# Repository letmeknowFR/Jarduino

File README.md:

<a href="#link"> _English version below_ :us: :arrow_down: </a>

> <p align="justify">Le Jarduino est un kit DIY permettant de créer un système de culture hydroponique et automatisé pour toutes sortes de plantes. Il permet de découvrir les concepts de l'agriculture hors-sol mais également de s'initier à l'électronique, la programmation, et l'impression 3D. Ce mini jardin est à faire soi-même. Modulable, personnalisable et évolutif selon vos envies, le Jarduino est Open Source : nous fournissons à tous les fichiers nécessaires pour réaliser les pieds, les panneaux latéraux et même la carte électronique. Il est donc très simple de s'approprier le projet afin de l'améliorer ou de le personnaliser.</p>

### Bill Of Materials :bookmark_tabs:
***
| Quantité |            Composant            |
|:--------:|:-------------------------------:|
|     1    | Carte électronique              |
|     1    | LCD 2 lignes 16 caractères I2C  |
|     1    | Jeu d'embases                   |
|     1    | Pompe USB                       |
|     1    | Lampe USB                       |
|     1    | Panier - Impression 3D          |
|     1    | Pied principal - Impression 3D  |
|     1    | Panneau supérieur               |
|     1    | Récipient                       |
|     1    | Durite                          |
|     1    | Alimentation                    |
|     3    | Pied angle - Impression 3D      |
|     4    | Panneaux latéraux               |

### Programmation :computer:
***
Tout d'abord placez la pile bouton (CR1220) dans son emplacement si cela n'est pas déjà fait. Ensuite, connectez l'écran à la carte principale via son connecteur, puis fixez-le à l'aide de l'embase prévue à cet effet.

Après avoir installé l'IDE Arduino, grâce au dossier fourni [software](/Software) ou directement sur le [site officiel](https://www.arduino.cc/en/Main/Software), installez les librairies qui se trouvent dans le dossier [librairies](/Software/Librairies) nécessaires à la compilation du programme principal "Jarduino.ino". Pour cela décompressez le contenu de l'archive dans votre répertoire Arduino/libraries.

Double-cliquez sur le programme ["Jarduino.ino"](/Software/Jarduino/Jarduino.ino).

Branchez votre carte via le connecteur USB, choisissez la carte "Leonardo" dans outils/type de carte et téléversez le programme !

Vous disposez également d'un programme de test ["Jarduino_test.ino"](/Software/Jarduino_Test/Jarduino_Test.ino). Il vous permettra de savoir si tous les composants électroniques fonctionnent correctement.

Vous voilà fin prêt ! Passons à la mécanique.

### Montage :wrench:
***
<p align="justify">Vous trouverez dans votre package mécanique: 3 pieds, 1 pied pour y placer la carte électronique, 4 panneaux de plastiques pour les côtés, 1 panneau pour le dessus. Montez le tout, remplissez 1/4 du récipient d'eau, ajoutez-y la lampe, la pompe, branchez l'alimentation et vous êtes fin prêt à faire pousser vos plantes.</p>

Vous pouvez bien sûr imprimer vos propres pieds et paniers grâce au dossier ["3D"](/3D).

### De la patience maintenant, la plante pousse ! :seedling:
***
***
<p align="center">  :us: </p>

>  <p align="justify">Jarduino is a DIY kit allowing to create a hydroponic and automated cultivation system for all kinds of plants . It allows to discover off-ground agriculture concepts and learn about electronics, programming, and 3D printing. This mini garden is a do it yourself project. Modular, customizable and scalable as you want, Jarduino is Open Source: we provide all necessary files to realize the feet, the side panels and even the electronic card. It's very simple to assimilate the project in order to improve it or to personalize it.</p>

### Bill Of Materials :bookmark_tabs:
***

| Quantity |            Components           |
|:--------:|:-------------------------------:|
|     1    | Electronic card                 |
|     1    | 2 line 16 character I2C LCD     |
|     1    | Header                          |
|     1    | USB Pump                        |
|     1    | USB Lamp                        |
|     1    | Basket - 3D printed             |
|     1    | Main foot - 3D printed          |
|     1    | Up pannel                       |
|     1    | Container                       |
|     1    | Hose                            |
|     1    | Alimentation                    |
|     3    | Angle foot - 3D printed         |
|     4    | Side pannel                     |

### Programming :computer:
***
First, place the button cell (CR1220) in its position if not already done. Then, connect the screen with the electronic card thanks to the 4-pin connector and fix it with the given headers.

After you installed Arduino, thanks to given folder ["software"](/Software) or the [official website](https://www.arduino.cc/en/Main/Software), install the libraries placed in the ["libraries"](/Software/Librairies) folder that make "Jarduino.ino" program compiled. To do that, uncompress the archive content in your Arduino/libraries folder.

Double-click on the program ["Jarduino.ino"](/Software/Jarduino/Jarduino.ino).

Connect the electronic card with your computer thank to the USB connector, choose "Leonardo" in tools/board option and upload the program!

You have a test program ["Jarduino_test.ino"](/Software/Jarduino_Test/Jarduino_Test.ino). It'll allow you to know if everything is ok.

You're all right! Let's move to the mechanical assembly.

### Mechanical assembly :wrench:
***
<p align="justify">You'll find in mechanical package: 3 feet, 1 main foot for the electronic card, 4 side panels, 1 panel for the top. Assemble it, fill a quarter of container with water, add the lamp, pump, power up and you're good to go!</p>

You can print your own 3D parts thanks to the given folder ["3D"](/3D).

### Patience now, plant is growing ! :seedling:

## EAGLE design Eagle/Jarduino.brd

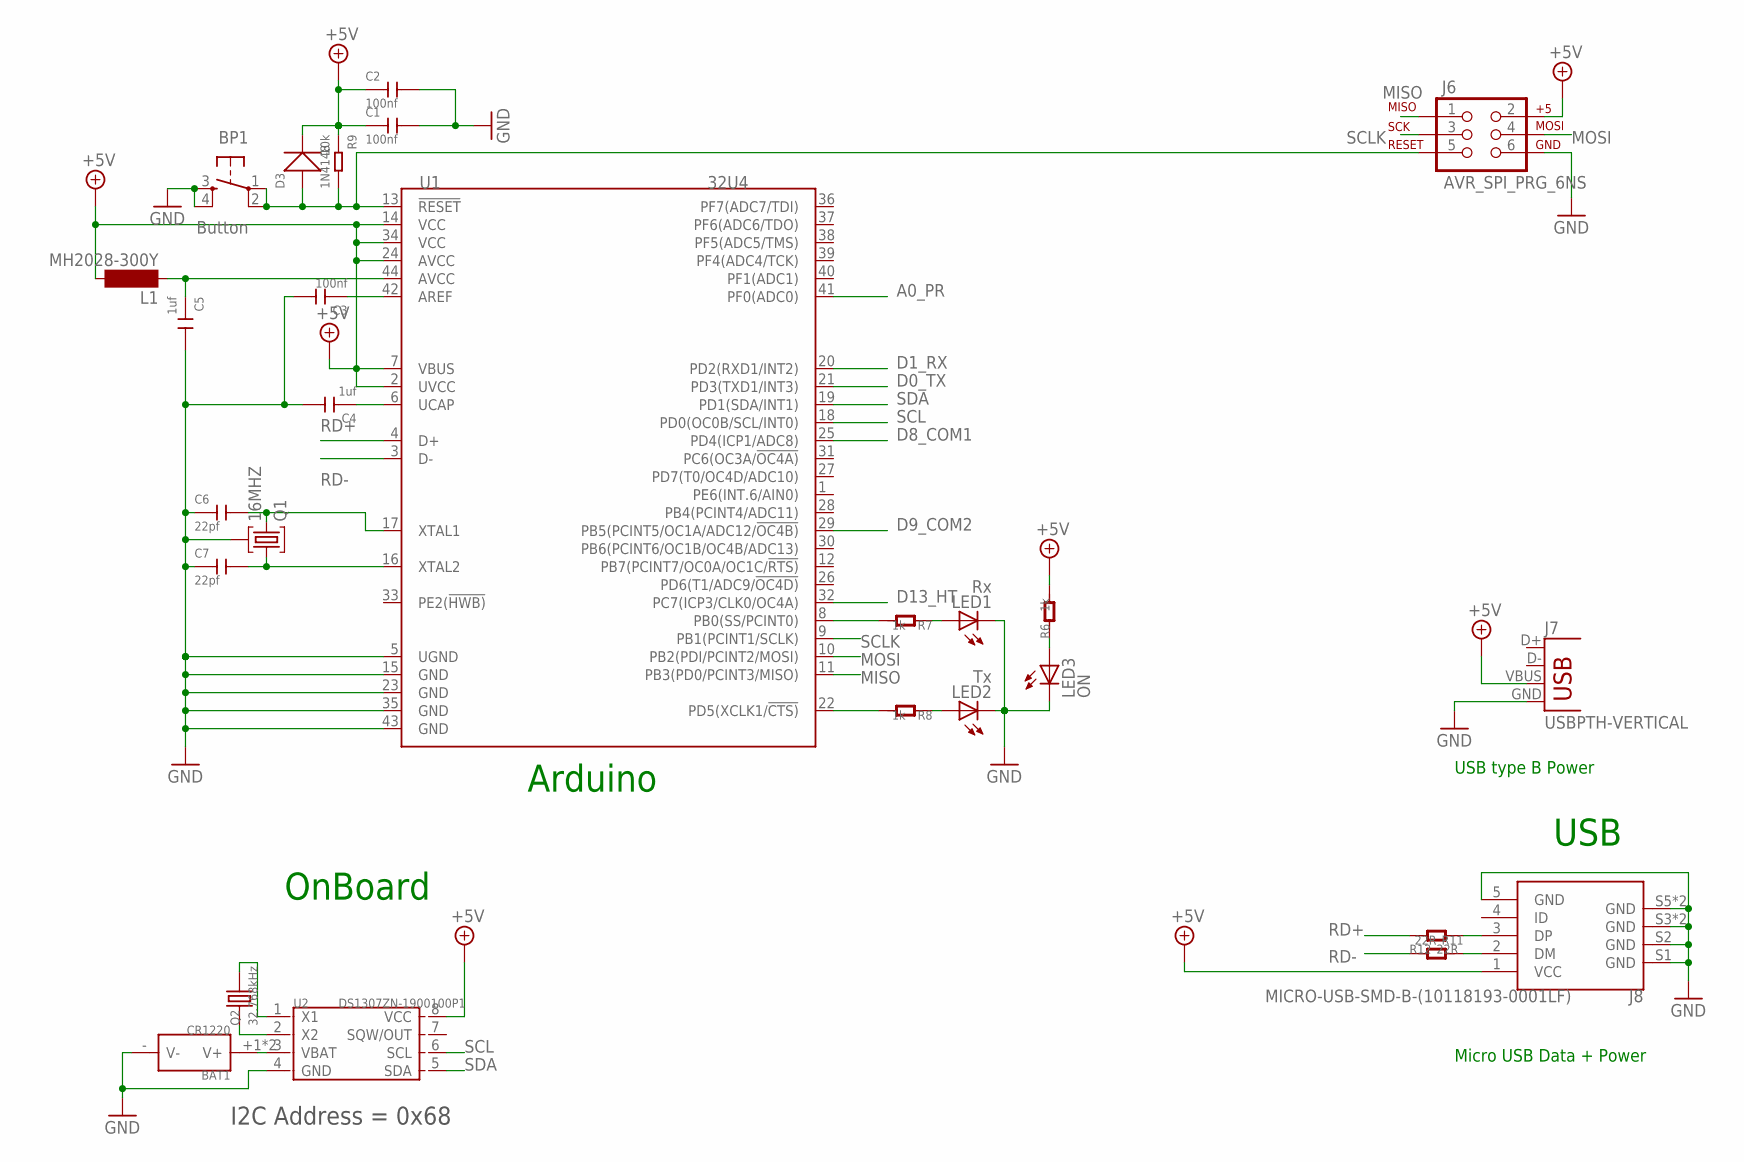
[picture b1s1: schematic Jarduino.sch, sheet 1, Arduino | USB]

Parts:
BAT1: CR1220; METAL-CR1220-D13.5XH5.0MM
BP1: Button; TACTILE-PTH
C1, C2, C3: 100nf; C0603
C4, C5: 1uf; C0603
C6, C7: 22pf; C0603
D3: 1N4148; LL-34
J6: AVR_SPI_PRG_6NS; 2X3-NS
J7: USBPTH-VERTICAL; USB-B-PTH-VERTICAL
J8: MICRO-USB-SMD-B-(10118193-0001LF); MICRO-USB5+6P-SMD-0.65-B
L1: MH2028-300Y; SM-1206
LED1: Rx; CHIP-LED0805
LED2: Tx; CHIP-LED0805
LED3: ON; CHIP-LED0805
Q1: 16MHZ; HC49U
Q2: 32.768kHz; 2P-L3.2XW1.5MM
R6, R7, R8: 1k; R0805
R9: 10k; R0805
R11, R12: 22R; R0805
U1: 32U4; TQFP44-0.8-9.6X9.6MM
U2: DS1307ZN-1900100P1; SOIC8

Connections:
+5V: C1.1, C2.1, D3.C (-), J6.2, J7.VBUS, J8.1 (VCC), L1.2, R6.2, R9.1, U1.2 (UVCC), U1.7 (VBUS), U1.14 (VCC), U1.24 (AVCC), U1.34 (VCC), U2.8 (VCC); also elsewhere on the board
A0_PR: U1.41 (PF0(ADC0)); also elsewhere on the board
D0_TX: U1.21 (PD3(TXD1/INT3)); also elsewhere on the board
D1_RX: U1.20 (PD2(RXD1/INT2)); also elsewhere on the board
D8_COM1: U1.25 (PD4(ICP1/ADC8)); also elsewhere on the board
D9_COM2: U1.29 (PB5(PCINT5/OC1A/ADC12/!OC4B)); also elsewhere on the board
D13_HT: U1.32 (PC7(ICP3/CLK0/OC4A)); also elsewhere on the board
GND: BAT1.- (V-), BP1.3, BP1.4, C1.2, C2.2, C3.2, C4.2, C5.2, C6.1, C7.1, J6.6, J7.GND, J8.5 (GND), J8.S1 (GND), J8.S2 (GND), J8.S3 (GND), J8.S4 (GND), J8.S5 (GND), J8.S6 (GND), LED1.C, LED2.C, LED3.C, Q1.2, U1.5 (UGND), U1.15 (GND), U1.23 (GND), U1.35 (GND), U1.43 (GND), U2.4 (GND); also elsewhere on the board
MISO: J6.1, U1.11 (PB3(PD0/PCINT3/MISO))
MOSI: J6.4, U1.10 (PB2(PDI/PCINT2/MOSI))
unnamed: LED3.A, R6.1
unnamed: R7.2, U1.8 (PB0(SS/PCINT0))
unnamed: J8.2 (DM), R12.2
unnamed: R8.2, U1.22 (PD5(XCLK1/!CTS))
unnamed: LED1.A, R7.1
unnamed: LED2.A, R8.1
unnamed: C6.2, Q1.3, U1.17 (XTAL1)
unnamed: C4.1, U1.6 (UCAP)
unnamed: C5.1, L1.1, U1.44 (AVCC)
unnamed: C3.1, U1.42 (AREF)
unnamed: C7.2, Q1.1, U1.16 (XTAL2)
unnamed: J8.3 (DP), R11.1
unnamed: Q2.2, U2.1 (X1)
unnamed: Q2.1, U2.2 (X2)
unnamed: BAT1.+1 (V+), BAT1.+2 (V+), U2.3 (VBAT)
RD+: R11.2, U1.4 (D+)
RD-: R12.1, U1.3 (D-)
RESET: BP1.1, BP1.2, D3.A (+), J6.5, R9.2, U1.13 (!RESET)
SCL: U1.18 (PD0(OC0B/SCL/INT0)), U2.6 (SCL); also elsewhere on the board
SCLK: J6.3, U1.9 (PB1(PCINT1/SCLK))
SDA: U1.19 (PD1(SDA/INT1)), U2.5 (SDA); also elsewhere on the board

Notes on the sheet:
Arduino
I2C Address = 0x68
OnBoard
USB
Micro USB Data + Power
USB type B Power

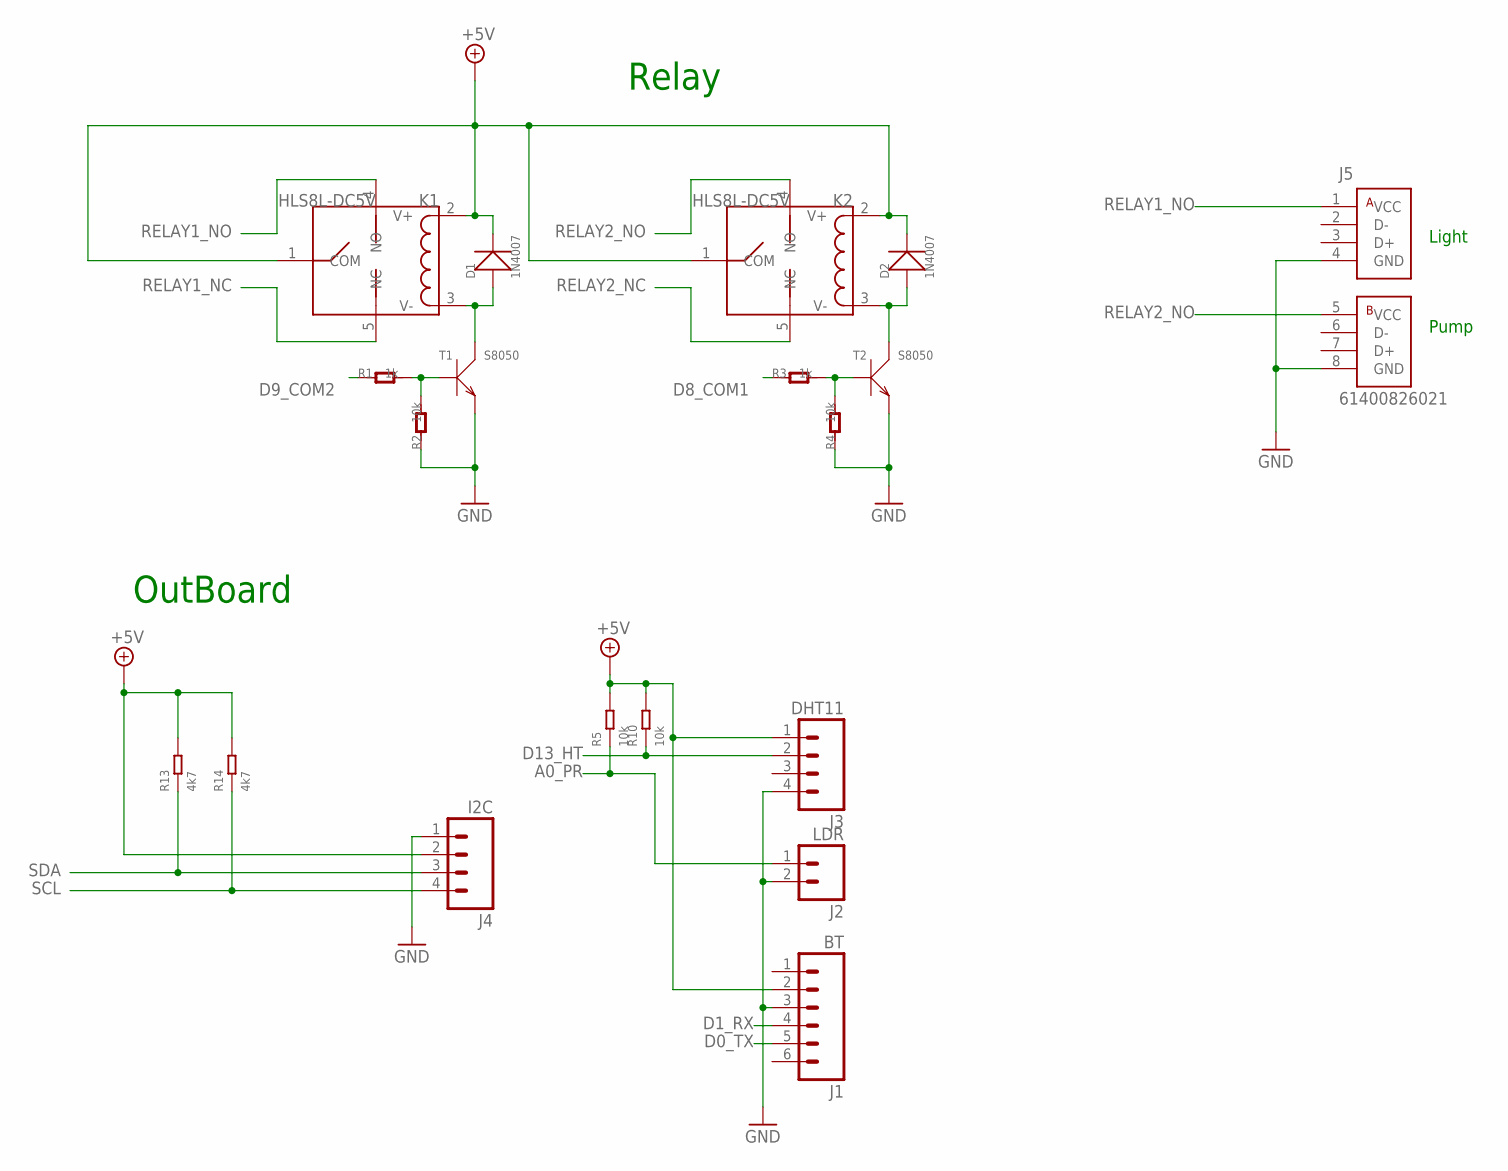
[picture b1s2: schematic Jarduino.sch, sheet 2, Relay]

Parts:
D1, D2: 1N4007; DO-214AC
J1: BT; MOLEX-1X6
J2: LDR; MOLEX-1X2
J3: DHT11; MOLEX-1X4
J4: I2C; MOLEX-1X4
J5: 61400826021
K1, K2: HLS8L-DC5V; 5P-L19.0XW15.0XH15.0MM
R1, R3: 1k; R0805
R2, R4, R5, R10: 10k; R0805
R13, R14: 4k7; R0805
T1, T2: S8050; SOT23

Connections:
+5V: D1.2 (-), D2.2 (-), J1.2, J3.1, J4.2, K1.1 (COM), K1.2 (V+), K2.1 (COM), K2.2 (V+), R5.2, R10.2, R13.2, R14.2; also elsewhere on the board
A0_PR: J2.1, R5.1; also elsewhere on the board
D0_TX: J1.5; also elsewhere on the board
D1_RX: J1.4; also elsewhere on the board
D8_COM1: R3.1; also elsewhere on the board
D9_COM2: R1.1; also elsewhere on the board
D13_HT: J3.2, R10.1; also elsewhere on the board
GND: J1.3, J2.2, J3.4, J4.1, J5.4 (GND), J5.8 (GND), R2.1, R4.1, T1.2 (E), T2.2 (E); also elsewhere on the board
unnamed: R3.2, R4.2, T2.1 (B)
unnamed: D2.1 (+), K2.3 (V-), T2.3 (C)
unnamed: R1.2, R2.2, T1.1 (B)
unnamed: D1.1 (+), K1.3 (V-), T1.3 (C)
RELAY1_NC: K1.5 (NC)
RELAY1_NO: J5.1 (VCC), K1.4 (NO)
RELAY2_NC: K2.5 (NC)
RELAY2_NO: J5.5 (VCC), K2.4 (NO)
SCL: J4.4, R14.1; also elsewhere on the board
SDA: J4.3, R13.1; also elsewhere on the board

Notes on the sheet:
Relay
OutBoard
Light
Pump

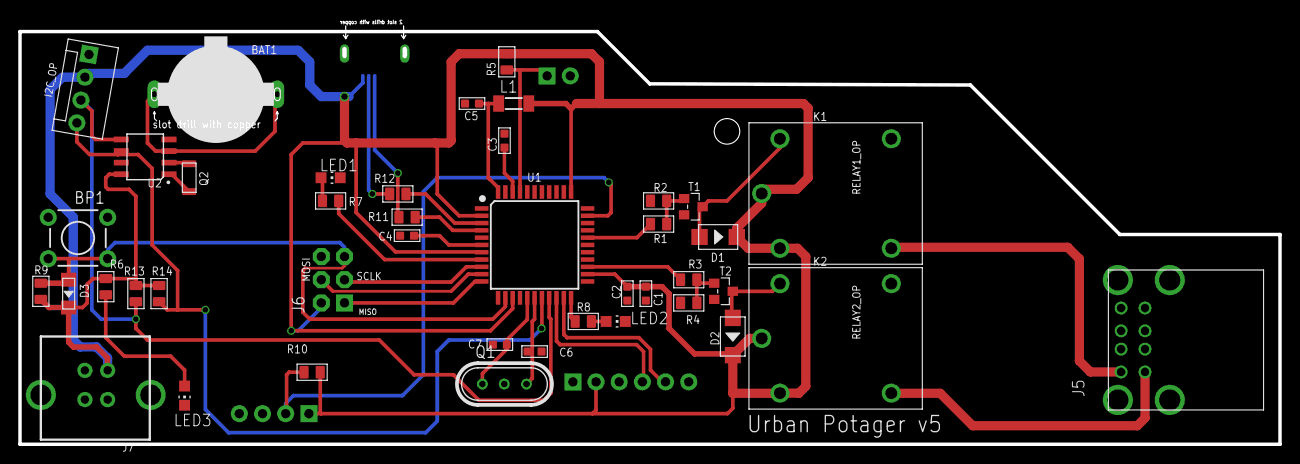
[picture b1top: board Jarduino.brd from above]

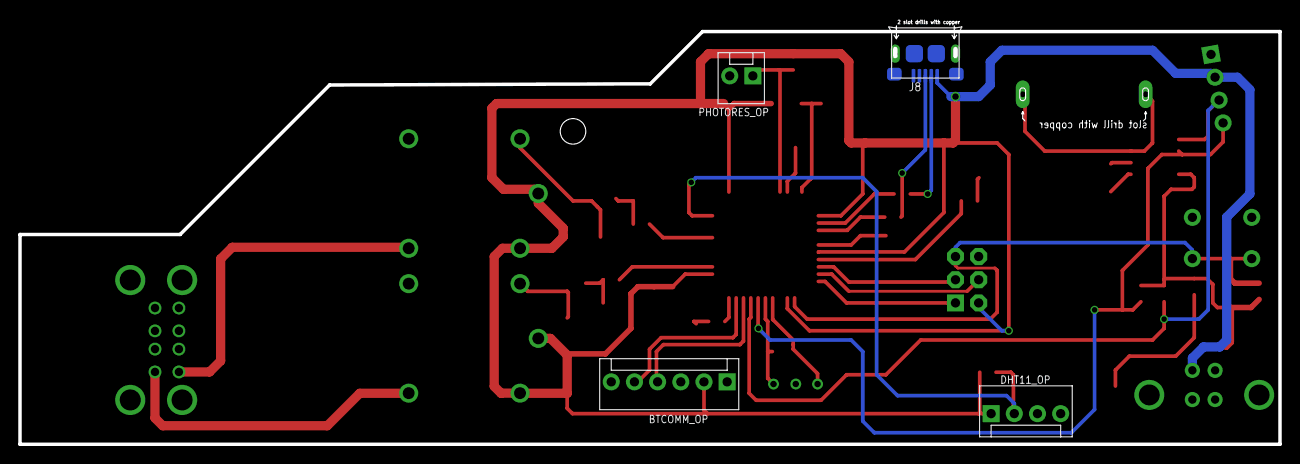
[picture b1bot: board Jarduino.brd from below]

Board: 2 copper layers, 137.9 x 46.4 mm, 46 parts (4 on the bottom side), 37 nets.

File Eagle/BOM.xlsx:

Name | Part | Value | Package | Description | Part NO. | Band
BAT1 | Battery holder | CR1220 | METAL-CR1220-D13.5XH5.0MM | Battery CR1220 holder
BP1 | Button | TAC_SWITCHPTH | TACTILE-PTH | Push button
C1, C2, C3 | Capacitor | 100nf 50V 10% | C0603 | Capacitor
C4, C5 | Capacitor | 100µf 50V 10% | C0603 | Capacitor
C6, C7 | Capacitor | 22pf 50V 10% | C0603 | Capacitor
D1, D2 | Diode | 1N4007 | DO-214AC | Diode
D3 | Diode | 1N4148 | LL-34 | Diode
J1 | Connector | M06POLAR | MOLEX-1X6 | Connector 6 points | Not implemented | Not implemented
J2 | Connector | M02POLAR | MOLEX-1X2 | Connector 2 points | Not implemented | Not implemented
J3, J4 | Connector | M04POLAR | MOLEX-1X4 | Connector 4 points | Not implemented | Not implemented
J5 | Connector | Double USB connector | 61400826021 | Double USB connector
J6 | Connector | AVR_SPI_PRG_6NS | 2X3-NS | Connector 2x3 points
J7 | Connector | USBPTH-VERTICAL | USB-B-PTH-VERTICAL | Connector USB type B vertical
J8 | Connector | MICRO-USB-SMD-B-(10118193-0001LF) | MICRO-USB5SMD-0.65-B Seee | Micro USB connector
K1, K2 | Relay | RELAY-HLS8L-DC5V-S-C-315030000 | 5P-L19.0XW15.0XH15.0MM | Relay 5V
L1 | Inductor | MH2028-300Y | SM-1206 | Inductor | Not implemented | Not implemented
LED1 | Rx | LEDCHIP-LED0805 | CHIP-LED0805 | led | Red LED | Generic
LED2 | Tx | LEDCHIP-LED0805 | CHIP-LED0805 | led | Red LED | Generic
LED3 | ON | LEDCHIP-LED0805 | CHIP-LED0805 | led | Green LED | Generic
Q1 | crystal | 16MHZ | HC49U | crystal
Q2 | crystal | 32.768kHz | 2P-L3.2XW1.5MM | crystal
R1, R3, R6, R7, R8 | Resistor | 1k | R0805 | Resistor | 1k | Generic
R2, R4, R5, R9, R10 | Resistor | 10k | R0805 | Resistor | 10k | Generic
R11, R12 | Resistor | 22R | R0805 | Resistor | 22R | Generic
R13, R14 | Resistor | 4k7 | R0805 | Resistor | 4k7 | Generic
T1, T2 | Transistor | S8050 | SOT23 | Transistor
U1 | Micro-controler | MCU-ATMEGA32U4(TQFP44)-AU | TQFP44-0.8-9.6X9.6MM | Micro-controler | ATMEGA32U4 | ATMEGA
U2 | RTC | DS1307ZN-1900100P1 | SOIC8 | RTC IC | DS1307ZN

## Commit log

2016-11-15 Add files
2017-10-18 Readme modif'
2017-12-03 Add Freecad files
    Freecad sources of the STL files
2018-02-28 Fixed a bug where the RTC would go back to the time/date of compilation after MCU reset. Ticket #310933
2018-05-29 Mise à jour des fichiers d'impressions
2018-08-01 adding small unit test of different components

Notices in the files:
parts and their libraries:
SparkFun-Connectors: Licensing: Creative Commons ShareAlike 4.0 International - https://creativecommons.org/licenses/by-sa/4.0
Eagle_INPUT_OUTPUT_CONNECTORS_rev15d: Copyright: Würth Elektronik
